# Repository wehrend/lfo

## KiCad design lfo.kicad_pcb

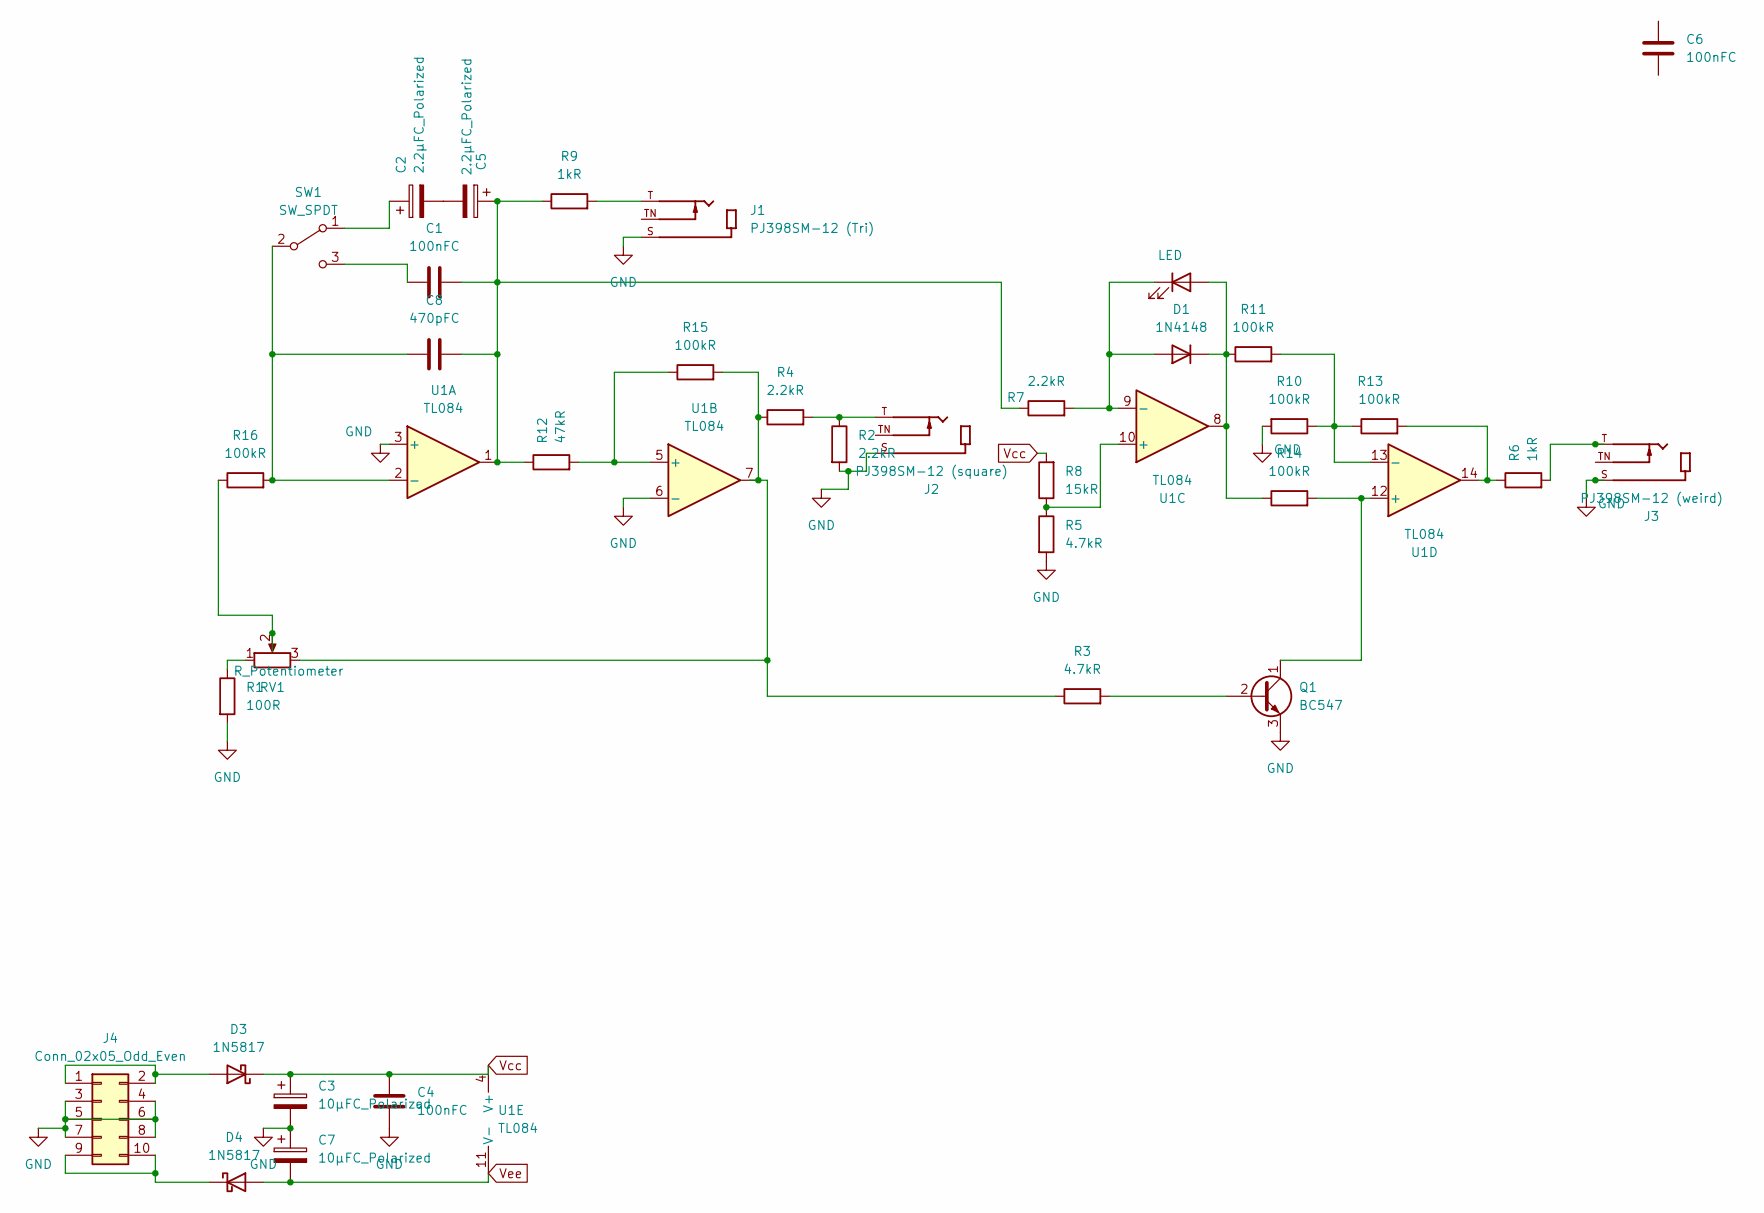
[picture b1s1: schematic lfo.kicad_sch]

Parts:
C1, C4: 100nFC; C_Disc_D4.7mm_W2.5mm_P5.00mm
C2, C5: 2.2µFC_Polarized; CP_Radial_D5.0mm_P2.00mm
C3, C7: 10µFC_Polarized; CP_Radial_D5.0mm_P2.00mm
C6: 100nFC; C_Disc_D9.0mm_W2.5mm_P5.00mm
C8: 470pFC; C_Disc_D9.0mm_W2.5mm_P5.00mm
D1: 1N4148; D_DO-41_SOD81_P2.54mm_Vertical_AnodeUp
D2: LED; LED_D5.0mm
D3, D4: 1N5817; D_DO-41_SOD81_P10.16mm_Horizontal
J1: PJ398SM-12 (Tri); Jack_3.5mm_QingPu_WQP-PJ398SM_Vertical_CircularHoles; PARTREV 1
J2: PJ398SM-12 (square); Jack_3.5mm_QingPu_WQP-PJ398SM_Vertical_CircularHoles; PARTREV 1
J3: PJ398SM-12 (weird); Jack_3.5mm_QingPu_WQP-PJ398SM_Vertical_CircularHoles; PARTREV 1
J4: Conn_02x05_Odd_Even; PinSocket_2x05_P2.54mm_Vertical
Q1: BC547; TO-92_Inline
R1: 100R; R_Axial_DIN0204_L3.6mm_D1.6mm_P5.08mm_Horizontal
R2, R4, R7: 2.2kR; R_Axial_DIN0204_L3.6mm_D1.6mm_P5.08mm_Horizontal
R3, R5: 4.7kR; R_Axial_DIN0204_L3.6mm_D1.6mm_P5.08mm_Horizontal
R6, R9: 1kR; R_Axial_DIN0204_L3.6mm_D1.6mm_P5.08mm_Horizontal
R8: 15kR; R_Axial_DIN0204_L3.6mm_D1.6mm_P5.08mm_Horizontal
R10, R11, R14, R15, R16: 100kR; R_Axial_DIN0204_L3.6mm_D1.6mm_P5.08mm_Horizontal
R12: 47kR; R_Axial_DIN0204_L3.6mm_D1.6mm_P5.08mm_Horizontal
R13: 100kR; R_Axial_DIN0204_L3.6mm_D1.6mm_P2.54mm_Vertical
RV1: R_Potentiometer; Potentiometer_Alpha_RD901F-40-00D_Single_Vertical
SW1: SW_SPDT; SW_100SP1T1B4M2QE
U1: TL084; DIP-14_W7.62mm_Socket_LongPads

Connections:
GND: C3.2, C4.2, C7.1, J1.S, J2.S, J3.S, J4.3, J4.4, J4.5, J4.6, J4.7, J4.8, Q1.3 (E), R1.2, R2.2, R5.2, R10.2, U1.3 (+), U1.6 (-)
unnamed: C1.2, C5.1, C8.2, R7.1, R9.1, R12.1, U1.1
unnamed: C2.2, C5.2
unnamed: D1.2 (A), D2.1 (K), R7.2, U1.9 (-)
unnamed: D1.1 (K), D2.2 (A), R11.1, R14.1, U1.8
unnamed: D3.2 (A), J4.1, J4.2
unnamed: D4.1 (K), J4.9, J4.10
unnamed: J1.T, R9.2
unnamed: J2.T, R2.1, R4.2
unnamed: J3.T, R6.2
unnamed: Q1.2 (B), R3.2
unnamed: Q1.1 (C), R14.2, U1.12 (+)
unnamed: R1.1, RV1.1
unnamed: R6.1, R13.2, U1.14
unnamed: R3.1, R4.1, R15.2, RV1.3, U1.7
unnamed: R16.1, RV1.2
unnamed: C2.1, SW1.1 (A)
unnamed: C8.1, R16.2, SW1.2 (B), U1.2 (-)
unnamed: C1.1, SW1.3 (C)
unnamed: R12.2, R15.1, U1.5 (+)
unnamed: R5.1, R8.1, U1.10 (+)
unnamed: R10.1, R11.2, R13.1, U1.13 (-)
Vcc: C3.1, C4.1, D3.1 (K), R8.2, U1.4 (V+)
Vee: C7.2, D4.2 (A), U1.11 (V-)

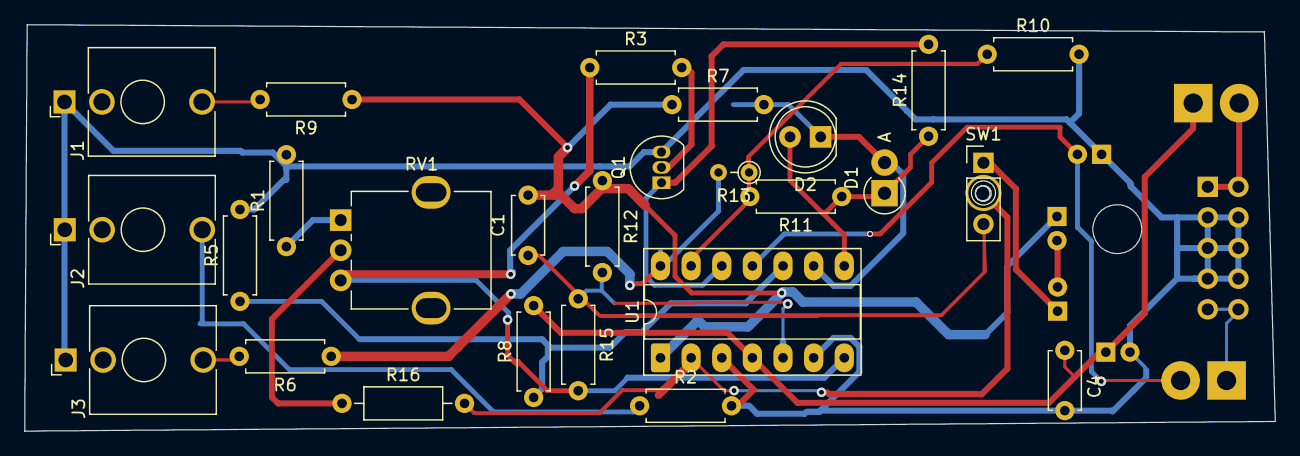
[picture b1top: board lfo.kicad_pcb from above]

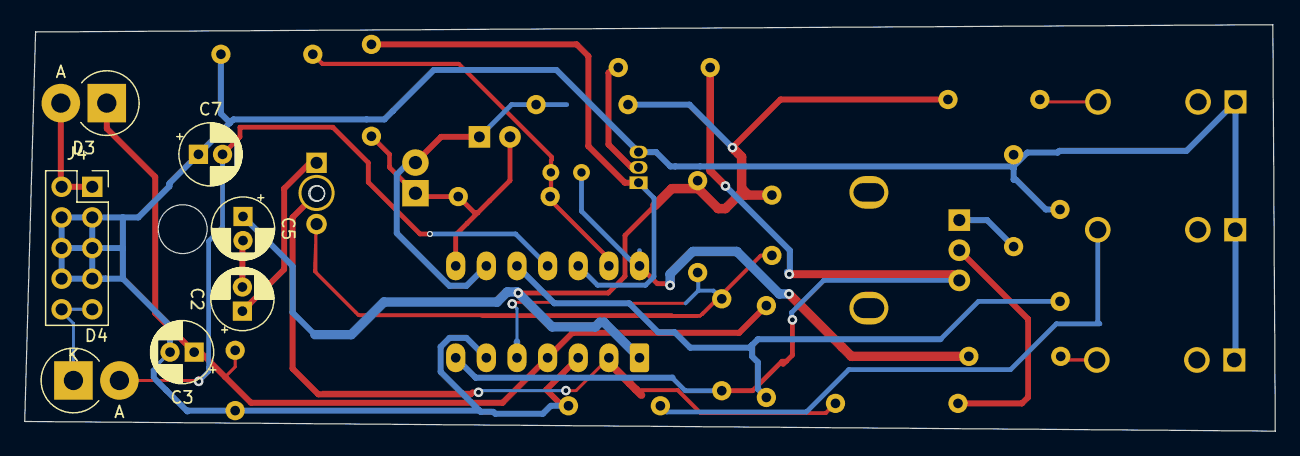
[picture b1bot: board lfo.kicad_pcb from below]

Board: 2 copper layers, 103.7 x 33.7 mm, 33 parts (7 on the bottom side), 24 nets.

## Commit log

2025-05-18 add mounting hole
2025-05-18 routing update
2025-05-18 remove redundant components
2025-05-18 successcive editing
2025-05-18 fix drc errors
2025-05-18 furter chnges
2025-05-18 finalize
2025-05-18 finalize (2)
2025-06-27 base commit
